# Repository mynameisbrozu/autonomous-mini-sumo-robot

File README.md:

## Autonomous mini sumo robot based on black pill STM32f411 microcontroller

## PCB in KiCad 
| Schematic | Routing |
|---|---|
|  |  |
## Pin selection - STM32F411

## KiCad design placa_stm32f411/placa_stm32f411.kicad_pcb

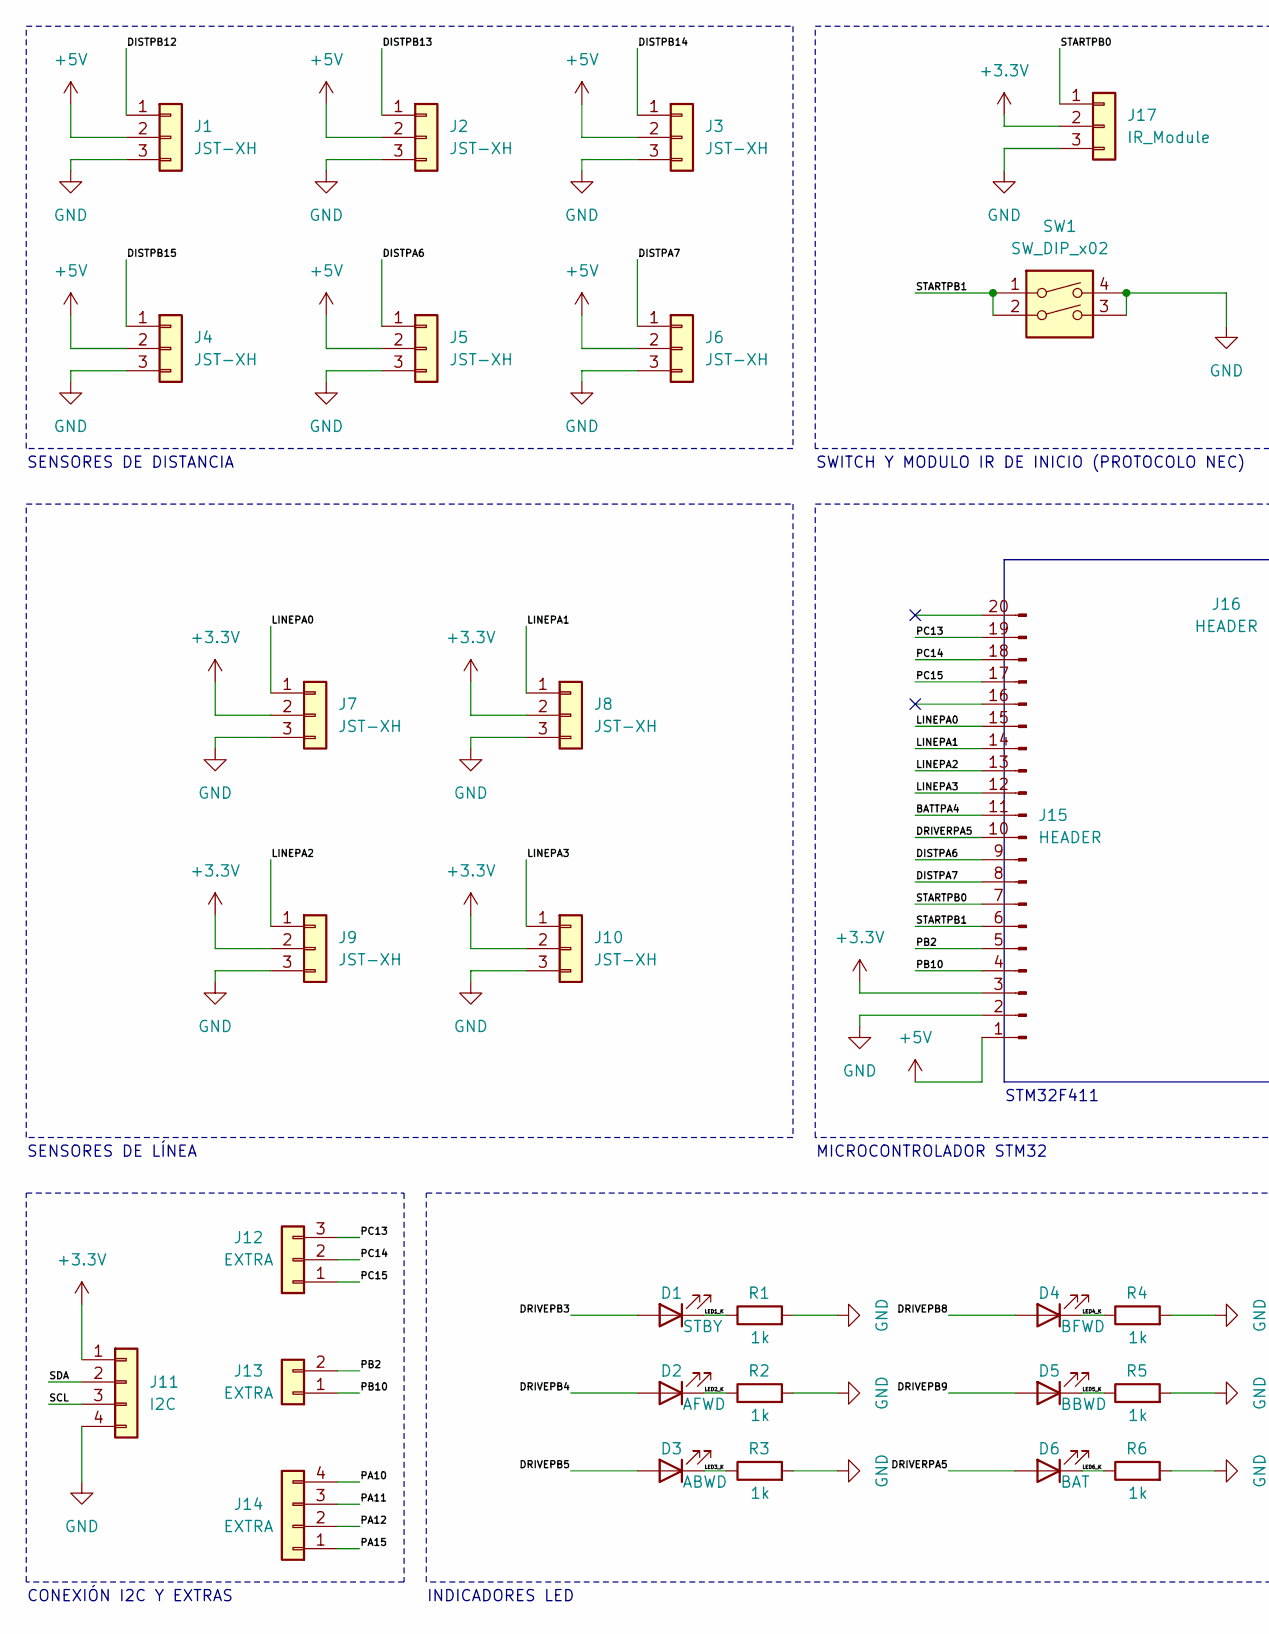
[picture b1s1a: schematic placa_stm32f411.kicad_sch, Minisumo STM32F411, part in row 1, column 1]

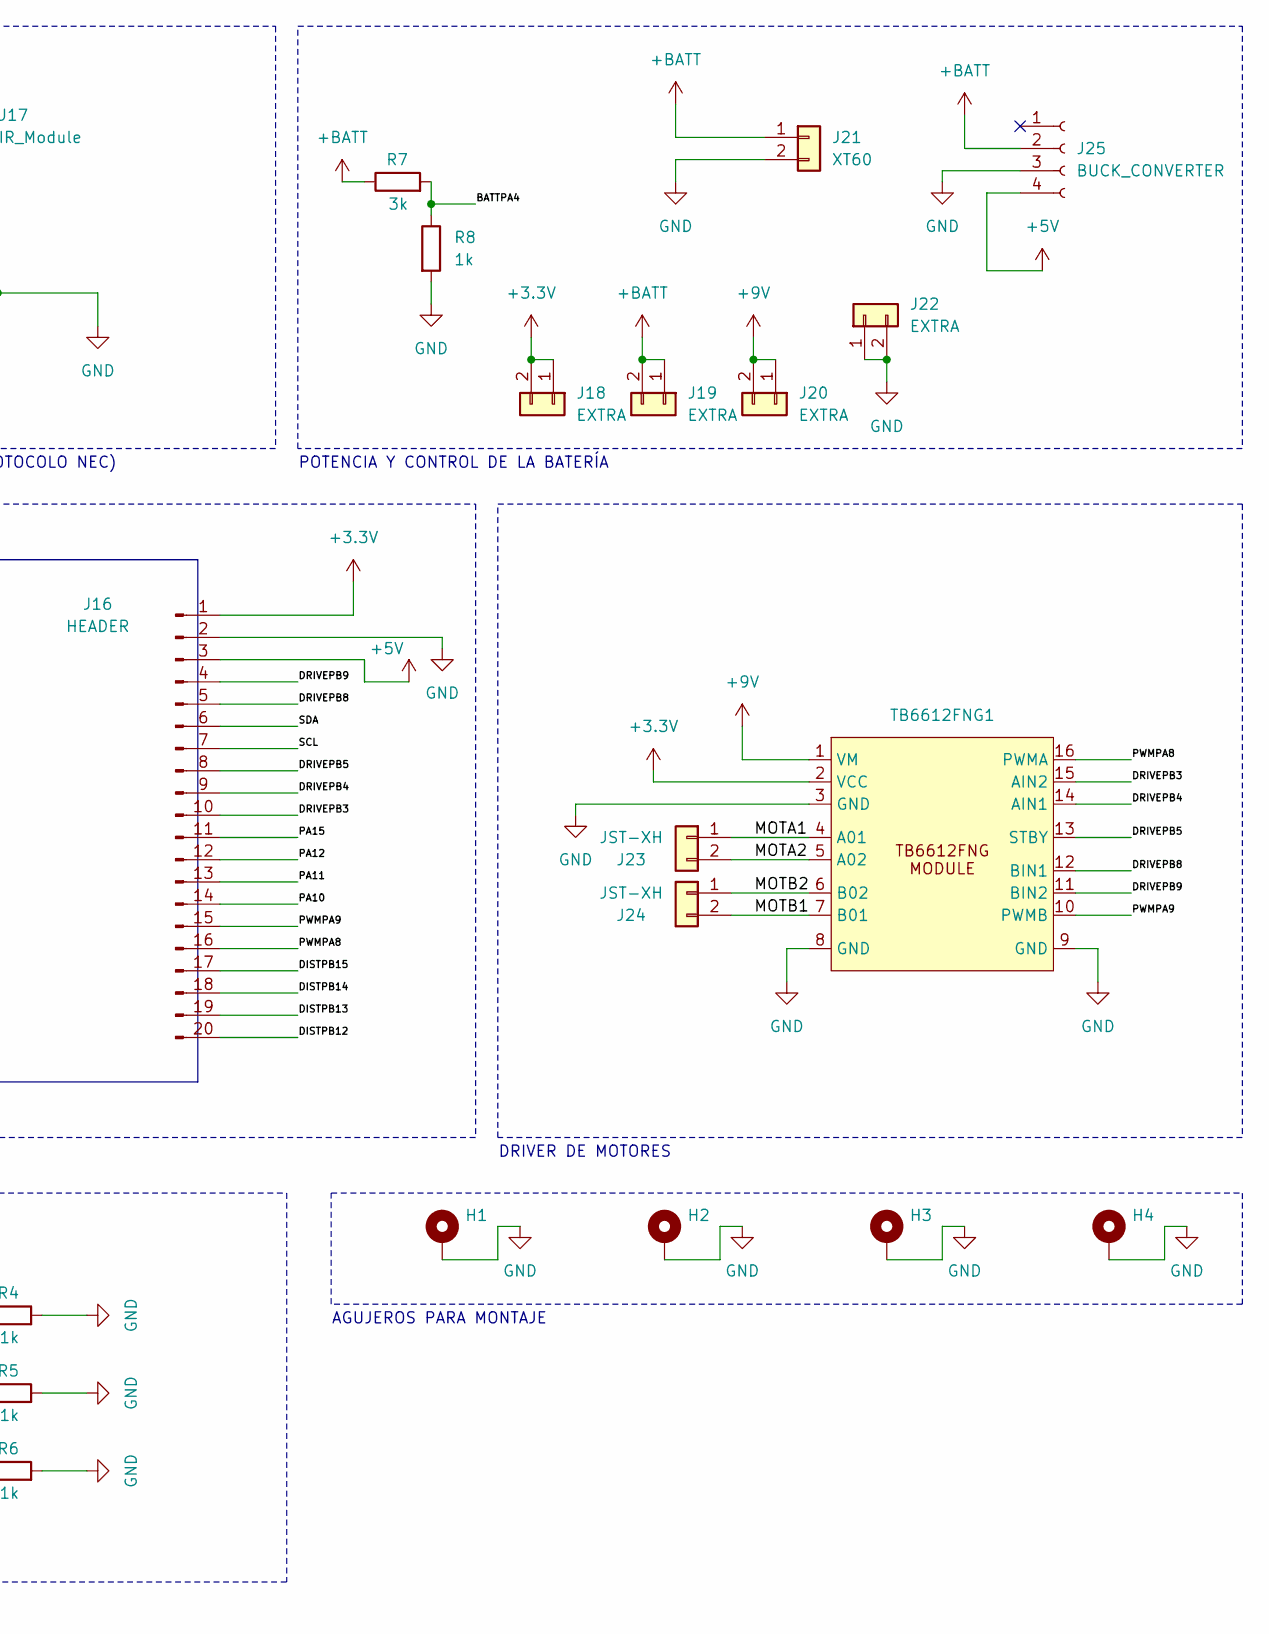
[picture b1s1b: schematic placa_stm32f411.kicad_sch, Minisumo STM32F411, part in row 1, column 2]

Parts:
D1: STBY; LED_1206_3216Metric_Pad1.42x1.75mm_HandSolder
D2: AFWD; LED_1206_3216Metric_Pad1.42x1.75mm_HandSolder
D3: ABWD; LED_1206_3216Metric_Pad1.42x1.75mm_HandSolder
D4: BFWD; LED_1206_3216Metric_Pad1.42x1.75mm_HandSolder
D5: BBWD; LED_1206_3216Metric_Pad1.42x1.75mm_HandSolder
D6: BAT; LED_1206_3216Metric_Pad1.42x1.75mm_HandSolder
H1, H2, H3, H4: MountingHole_Pad; MountingHole_3.2mm_M3_Pad_Via
J1, J2, J3, J4, J5, J6, J7, J8, J9, J10: JST-XH; JST_XH_B3B-XH-A_1x03_P2.50mm_Vertical
J11: I2C; PinHeader_1x04_P2.00mm_Vertical_SMD_Pin1Left
J12: EXTRA; PinHeader_1x03_P2.00mm_Vertical_SMD_Pin1Left
J13, J18, J19, J20, J22: EXTRA; PinHeader_1x02_P2.00mm_Vertical_SMD_Pin1Left
J14: EXTRA; PinHeader_1x04_P2.00mm_Vertical_SMD_Pin1Left
J15, J16: HEADER; PinSocket_1x20_P2.54mm_Vertical
J17: IR_Module; PinSocket_1x03_P2.54mm_Vertical
J21: XT60; AMASS_XT60PW-M_1x02_P7.20mm_Horizontal
J23, J24: JST-XH; JST_XH_S2B-XH-A-1_1x02_P2.50mm_Horizontal
J25: BUCK_CONVERTER; PinSocket_1x04_P2.54mm_Vertical
R1, R2, R3, R4, R5, R6, R8: 1k; R_1206_3216Metric_Pad1.30x1.75mm_HandSolder
R7: 3k; R_1206_3216Metric_Pad1.30x1.75mm_HandSolder
SW1: SW_DIP_x02; SW_DIP_SPSTx02_Slide_9.78x7.26mm_W7.62mm_P2.54mm
TB6612FNG1: TB6612FNG_Module

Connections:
+3.3V: J7.2, J8.2, J9.2, J10.2, J11.1, J15.3, J16.1, J17.2, J18.1, J18.2, TB6612FNG1.2 (VCC); also elsewhere on the board
+5V: J1.2, J2.2, J3.2, J4.2, J5.2, J6.2, J15.1, J16.3, J25.4
+9V: J20.1, J20.2, TB6612FNG1.1 (VM); also elsewhere on the board
+BATT: J19.1, J19.2, J21.1, J25.2, R7.1
/BATTPA4: J15.11, R7.2, R8.1
/DISTPA6: J5.1, J15.9
/DISTPA7: J6.1, J15.8
/DISTPB12: J1.1, J16.20
/DISTPB13: J2.1, J16.19
/DISTPB14: J3.1, J16.18
/DISTPB15: J4.1, J16.17
/DRIVEPB3: D1.2 (A), J16.10, TB6612FNG1.15 (AIN2); also elsewhere on the board
/DRIVEPB4: D2.2 (A), J16.9, TB6612FNG1.14 (AIN1); also elsewhere on the board
/DRIVEPB5: D3.2 (A), J16.8, TB6612FNG1.13 (STBY); also elsewhere on the board
/DRIVEPB8: D4.2 (A), J16.5, TB6612FNG1.12 (BIN1); also elsewhere on the board
/DRIVEPB9: D5.2 (A), J16.4, TB6612FNG1.11 (BIN2); also elsewhere on the board
/DRIVERPA5: D6.2 (A), J15.10
/LED1_K: D1.1 (K), R1.1
/LED2_K: D2.1 (K), R2.1
/LED3_K: D3.1 (K), R3.1
/LED4_K: D4.1 (K), R4.1
/LED5_K: D5.1 (K), R5.1
/LED6_K: D6.1 (K), R6.1
/LINEPA0: J7.1, J15.15
/LINEPA1: J8.1, J15.14
/LINEPA2: J9.1, J15.13
/LINEPA3: J10.1, J15.12
/MOTA1: J23.1, TB6612FNG1.4 (A01); also elsewhere on the board
/MOTA2: J23.2, TB6612FNG1.5 (A02); also elsewhere on the board
/MOTB1: J24.2, TB6612FNG1.7 (B01); also elsewhere on the board
/MOTB2: J24.1, TB6612FNG1.6 (B02); also elsewhere on the board
/PA10: J14.4, J16.14
/PA11: J14.3, J16.13
/PA12: J14.2, J16.12
/PA15: J14.1, J16.11
/PB2: J13.2, J15.5
/PB10: J13.1, J15.4
/PC13: J12.3, J15.19
/PC14: J12.2, J15.18
/PC15: J12.1, J15.17
/PWMPA8: J16.16, TB6612FNG1.16 (PWMA); also elsewhere on the board
/PWMPA9: J16.15, TB6612FNG1.10 (PWMB); also elsewhere on the board
/SCL: J11.3, J16.7
/SDA: J11.2, J16.6
/STARTPB0: J15.7, J17.1
/STARTPB1: J15.6, SW1.1, SW1.2
GND: H1.1, H2.1, H3.1, H4.1, J1.3, J2.3, J3.3, J4.3, J5.3, J6.3, J7.3, J8.3, J9.3, J10.3, J11.4, J15.2, J16.2, J17.3, J21.2, J22.1, J22.2, J25.3, R1.2, R2.2, R3.2, R4.2, R5.2, R6.2, R8.2, SW1.3, SW1.4, TB6612FNG1.3 (GND), TB6612FNG1.8 (GND), TB6612FNG1.9 (GND); also elsewhere on the board

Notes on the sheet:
AGUJEROS PARA MONTAJE
MICROCONTROLADOR STM32
DRIVER DE MOTORES
SENSORES DE LÍNEA
STM32F411
CONEXIÓN I2C Y EXTRAS
SENSORES DE DISTANCIA
SWITCH Y MODULO IR DE INICIO (PROTOCOLO NEC)
INDICADORES LED
POTENCIA Y CONTROL DE LA BATERÍA

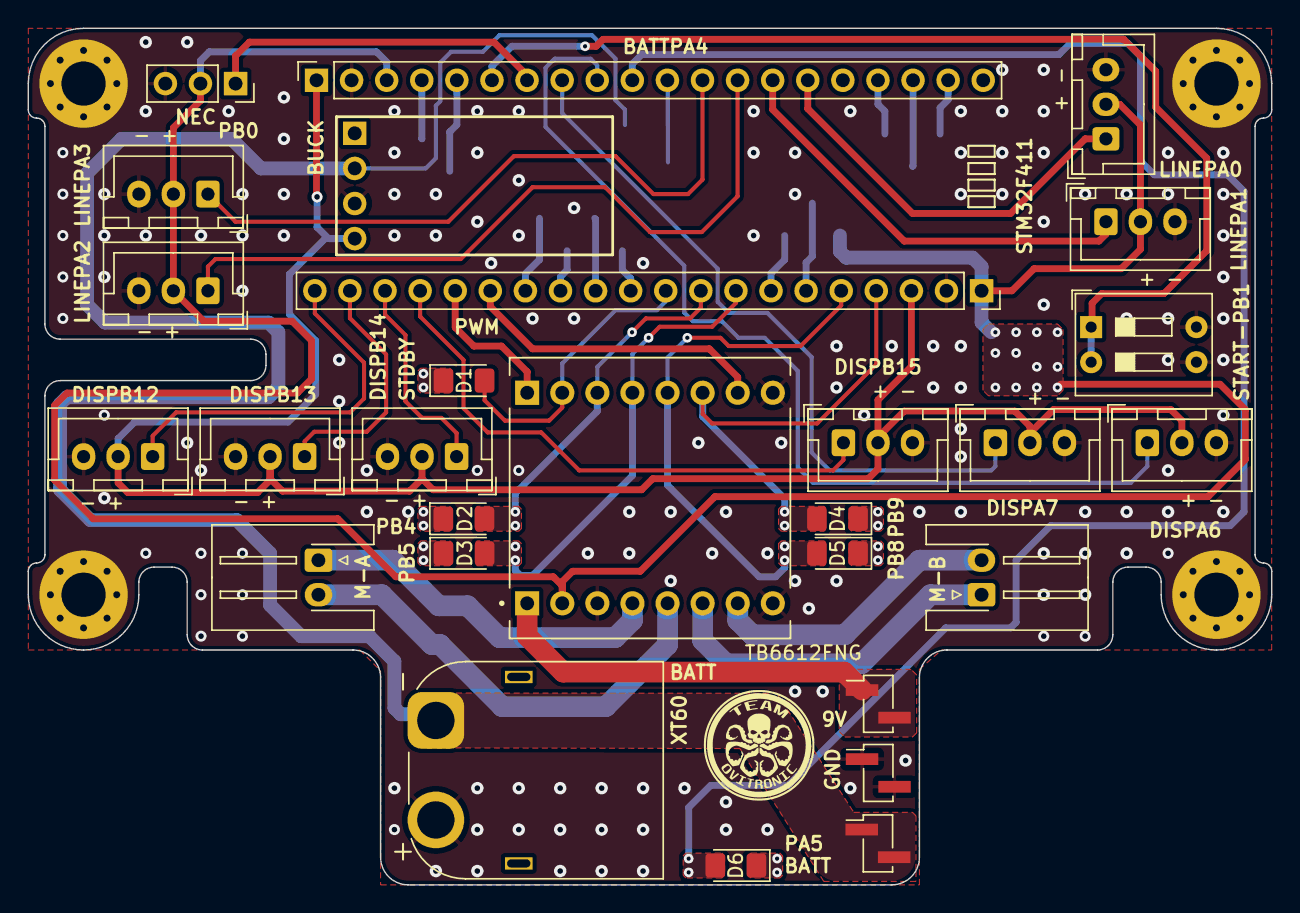
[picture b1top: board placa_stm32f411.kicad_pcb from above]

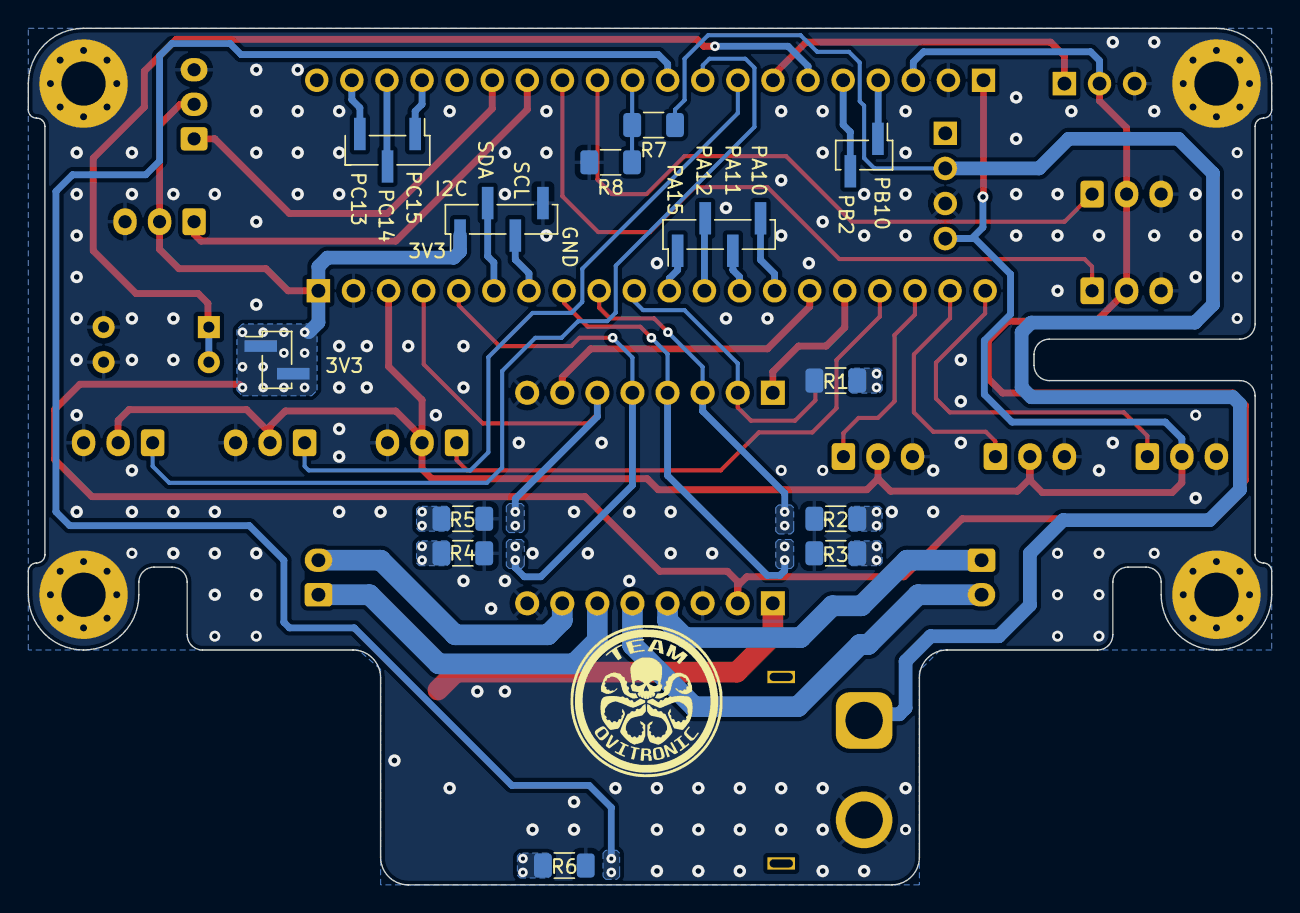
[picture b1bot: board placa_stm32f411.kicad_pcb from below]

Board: 2 copper layers, 90.0 x 62.0 mm, 45 parts (13 on the bottom side), 47 nets.

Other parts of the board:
TB6612FNG: TB6612FNG_Module

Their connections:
+3.3V: TB6612FNG.2 (VCC); also elsewhere on the board
+9V: TB6612FNG.1 (VM); also elsewhere on the board
/DRIVEPB3: TB6612FNG.15 (AIN2); also elsewhere on the board
/DRIVEPB4: TB6612FNG.14 (AIN1); also elsewhere on the board
/DRIVEPB5: TB6612FNG.13 (STBY); also elsewhere on the board
/DRIVEPB8: TB6612FNG.12 (BIN1); also elsewhere on the board
/DRIVEPB9: TB6612FNG.11 (BIN2); also elsewhere on the board
/MOTA1: TB6612FNG.4 (A01); also elsewhere on the board
/MOTA2: TB6612FNG.5 (A02); also elsewhere on the board
/MOTB1: TB6612FNG.7 (B01); also elsewhere on the board
/MOTB2: TB6612FNG.6 (B02); also elsewhere on the board
/PWMPA8: TB6612FNG.16 (PWMA); also elsewhere on the board
/PWMPA9: TB6612FNG.10 (PWMB); also elsewhere on the board
GND: TB6612FNG.3 (GND), TB6612FNG.8 (GND), TB6612FNG.9 (GND); also elsewhere on the board

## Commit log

2026-02-20 files upload
2026-02-20 stm32f411 pin upload
2026-02-20 pendent: firmware
